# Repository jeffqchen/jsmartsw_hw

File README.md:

# jsmartsw_hw

This is the hardware repository of the jSmartSW project.

The hardware is consisted of two parts. The jSmartSW mainboard contains the main I/O and logic board. The keypad contains visual feedback interfaces and tactile inputs.

Detailed building guides and technical details are documented in the project wiki pages.

For functionality and day-to-day usage, please refer to the [main project repository](https://github.com/jeffqchen/jSmartSW)

## Primary Parts

### Main Board

The main board interfaces with and utilizes a Raspberry Pi Pico to run the logic programs of this project. The main board is needed for the project.

The main board has many ports for power and I/O:
- **Power**
  - **DC 5V barrel jack** (optional)

    The preferred source to power jSmartSW.
    
  - **USB-C jack** (optional)
 
    USB functionality is provided via this port. You can also power the jSmartSW from this port.

  - **Toggle switch** (optional)
    
    For turning the power from the barrel jack and USB-C jack on or off.

- **Video & Audio**
  - **HD15 video/audio passthrough input** (optional, recommended):
    
    Since the project communicates to the RetroTink 4K primarily via the HD15 port, you can connect HD15 sources to this port and feed it to the RetroTink 4K.
    
  - **HD15 video passthrough output** (optional):
    
    The video input from the passthrough input port is output from this port. The serial control commands are sent from this port to the RetroTink 4K if a USB-C connection is not present to the RetroTink 4K.
    
  - **3.5mm TRS barrel jack**:
    
    Audio signal input from the passthrough input pin 12 & 15 is broken out to this port, so you can use a 3.5mm TRS audio cable and feed it to the RetroTink 4K.

- **Communication**
  - **2x4 right-angle pin header**:
  
    Communicates with the gSCARTsw.
    
  - **2x7 right-angle pin header** (optional):

    Communicates with the optional keypad.
    
  - **HD15 video passthrough output** (already listed):

    The serial control commands are sent from this port to the RetroTink 4K if a USB-C connection is not present to the RetroTink 4K.
    
  - **USB-C jack** (already listed):

    When connected to the RetroTink 4K, it will become the preferred channel of communication. It also supplies power into the RetroTink 4K. In this case, the 5V barreljack must be populated as the main source of power.

### Keypad

The keypad is the primary user interface of jSmartSW. It has a screen, addressable RGB LEDs, and 8 key switches.

- Screen

  A 0.91 inch OLED SSD1306 screen at 128x32 resolution.

- 16 (8x2) WS2812b OR WS2812b 2020 addressable RGB LEDs.

  An array of addressabvle RGB LEDs for indicating device running state and prodiving visual assistance.
  
- 8x Cherry MX keyboard switches with XDA key caps

  An array of keyboard switches for controlling functionalities of jSmartSW.

- Keypad Faceplate Panel

  Cosmetic face panel with markings. Markings will be illuminated by the RGB LEDs.

- 3D printed Keypad body shell & light shroud

------
Shield: [![CC BY-SA 4.0][cc-by-sa-shield]][cc-by-sa]

This work is licensed under a
[Creative Commons Attribution-ShareAlike 4.0 International License][cc-by-sa].

[![CC BY-SA 4.0][cc-by-sa-image]][cc-by-sa]

[cc-by-sa]: http://creativecommons.org/licenses/by-sa/4.0/
[cc-by-sa-image]: https://licensebuttons.net/l/by-sa/4.0/88x31.png
[cc-by-sa-shield]: https://img.shields.io/badge/License-CC%20BY--SA%204.0-lightgrey.svg

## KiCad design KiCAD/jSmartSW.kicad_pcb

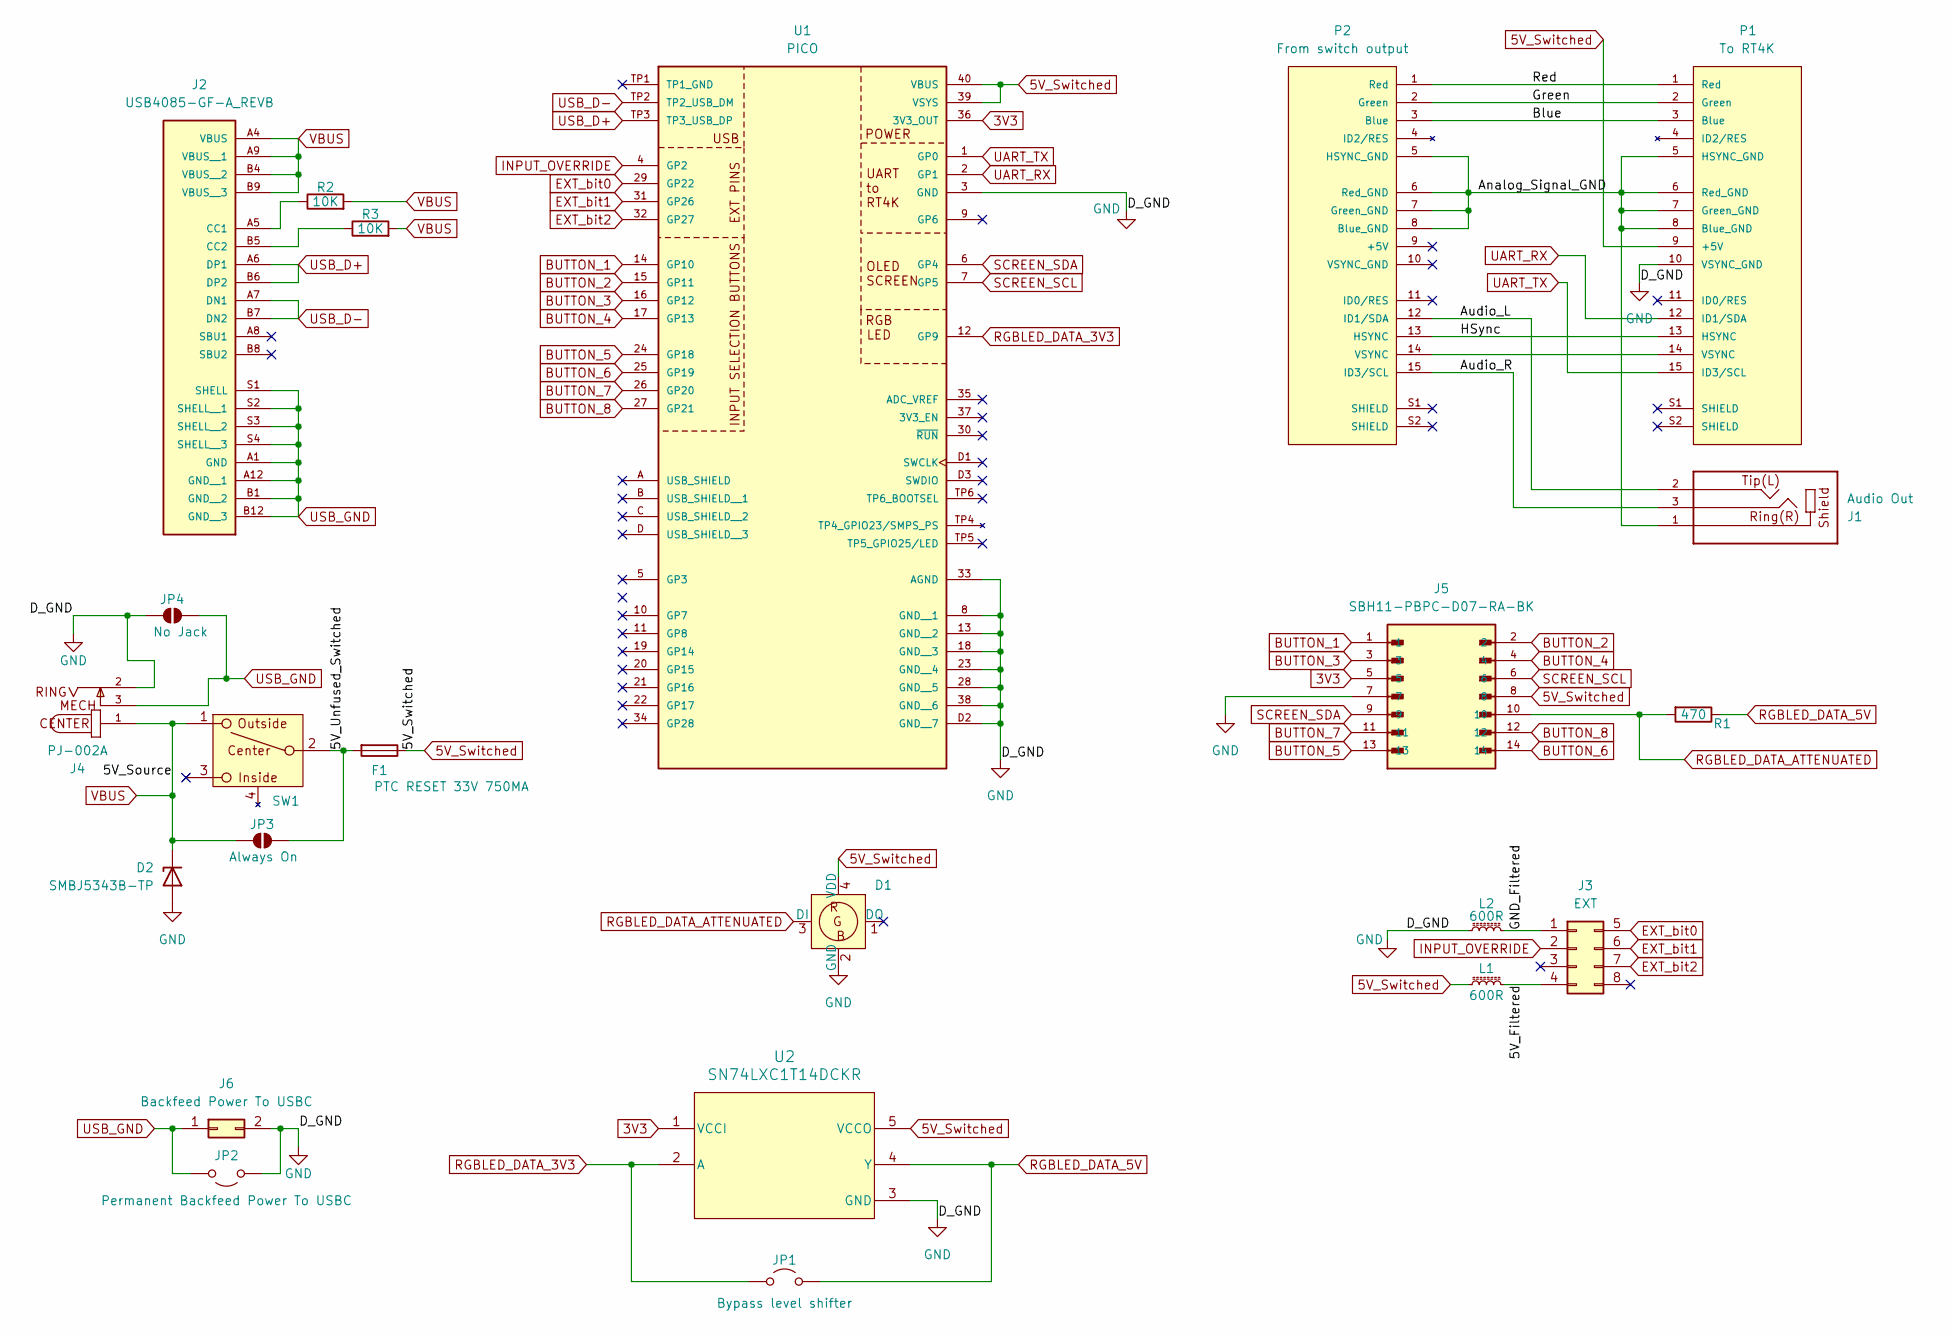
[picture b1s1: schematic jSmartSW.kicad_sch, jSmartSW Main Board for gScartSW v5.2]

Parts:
D1: WS2812b_2020
D2: SMBJ5343B-TP; D_SMB
F1: PTC RESET 33V 750MA; Fuse_1812_4532Metric_Pad1.30x3.40mm_HandSolder
J1: Audio Out; 3.5mm_jack_horizontal; PARTREV 1.02
J2: USB4085-GF-A_REVB; GCT_USB4085-GF-A_REVB; PARTREV B
J3: EXT; PinHeader_2x04_P2.54mm_Horizontal
J4: PJ-002A; CUI_PJ-002A
J5: SBH11-PBPC-D07-RA-BK; SULLINS_SBH11-PBPC-D07-RA-BK; PARTREV J
J6: Backfeed Power To USBC; PinHeader_1x02_P2.54mm_Horizontal
JP1: Bypass level shifter; SolderJumper-2_P1.3mm_Open_RoundedPad1.0x1.5mm
JP2: Permanent Backfeed Power To USBC; SolderJumper-2_P1.3mm_Bridged2Bar_RoundedPad1.0x1.5mm
JP3: Always On; SolderJumper-2_P1.3mm_Open_RoundedPad1.0x1.5mm
JP4: No Jack; SolderJumper-2_P1.3mm_Open_RoundedPad1.0x1.5mm
L1, L2: 600R; L_1206_3216Metric_Pad1.22x1.90mm_HandSolder
P1: To RT4K; VGA_female_rightangle_slim; PARTREV N/A
P2: From switch output; VGA_male_rightangle_slim; PARTREV N/A
R1: 470; R_0805_2012Metric_Pad1.20x1.40mm_HandSolder
R2, R3: 10K; R_0603_1608Metric_Pad0.98x0.95mm_HandSolder
SW1: BST13T1AVR
U1: PICO; RP2040_PICO; PARTREV 1.9
U2: SN74LXC1T14DCKR; DCK0005A-IPC_A

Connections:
3V3: J5.5, U1.36 (3V3_OUT), U2.1 (VCCI)
5V_Switched: D1.4 (VDD), F1.1, J5.8, L1.1, P1.9 (+5V), U1.39 (VSYS), U1.40 (VBUS), U2.5 (VCCO)
/5V_Filtered: J3.4, L1.2
/5V_Unfused_Switched: F1.2, JP3.1 (A), SW1.2 (Center)
/Analog_Signal_GND: J1.1, P1.5 (HSYNC_GND), P1.6 (Red_GND), P1.7 (Green_GND), P1.8 (Blue_GND), P2.5 (HSYNC_GND), P2.6 (Red_GND), P2.7 (Green_GND), P2.8 (Blue_GND)
/Audio_L: J1.2, P2.12 (ID1/SDA)
/Audio_R: J1.3, P2.15 (ID3/SCL)
/Blue: P1.3 (Blue), P2.3 (Blue)
/GND_Filtered: J3.1, L2.2
/Green: P1.2 (Green), P2.2 (Green)
/HSync: P1.13 (HSYNC), P2.13 (HSYNC)
/Red: P1.1 (Red), P2.1 (Red)
BUTTON_1: J5.1, U1.14 (GP10)
BUTTON_2: J5.2, U1.15 (GP11)
BUTTON_3: J5.3, U1.16 (GP12)
BUTTON_4: J5.4, U1.17 (GP13)
BUTTON_5: J5.13, U1.24 (GP18)
BUTTON_6: J5.14, U1.25 (GP19)
BUTTON_7: J5.11, U1.26 (GP20)
BUTTON_8: J5.12, U1.27 (GP21)
EXT_bit0: J3.5, U1.29 (GP22)
EXT_bit1: J3.6, U1.31 (GP26)
EXT_bit2: J3.7, U1.32 (GP27)
GND: D1.2 (GND), D2.2 (A), J4.2, J5.7, J6.2, JP2.1 (A), JP4.2 (B), L2.1, P1.10 (VSYNC_GND), U1.3 (GND), U1.8 (GND__1), U1.13 (GND__2), U1.18 (GND__3), U1.23 (GND__4), U1.28 (GND__5), U1.33 (AGND), U1.38 (GND__6), U1.D2 (GND__7), U2.3 (GND)
INPUT_OVERRIDE: J3.2, U1.4 (GP2)
unnamed: J2.A5 (CC1), R2.1
unnamed: J2.B5 (CC2), R3.1
unnamed: P1.14 (VSYNC), P2.14 (VSYNC)
RGBLED_DATA_3V3: JP1.1 (A), U1.12 (GP9), U2.2 (A)
RGBLED_DATA_5V: JP1.2 (B), R1.1, U2.4 (Y)
RGBLED_DATA_ATTENUATED: D1.3 (DI), J5.10, R1.2
SCREEN_SCL: J5.6, U1.7 (GP5)
SCREEN_SDA: J5.9, U1.6 (GP4)
UART_RX: P1.12 (ID1/SDA), U1.2 (GP1)
UART_TX: P1.15 (ID3/SCL), U1.1 (GP0)
USB_D+: J2.A6 (DP1), J2.B6 (DP2), U1.TP3 (TP3_USB_DP)
USB_D-: J2.A7 (DN1), J2.B7 (DN2), U1.TP2 (TP2_USB_DM)
USB_GND: J2.A1 (GND), J2.A12 (GND__1), J2.B1 (GND__2), J2.B12 (GND__3), J2.S1 (SHELL), J2.S2 (SHELL__1), J2.S3 (SHELL__2), J2.S4 (SHELL__3), J4.3, J6.1, JP2.2 (B), JP4.1 (A)
VBUS: D2.1 (K), J2.A4 (VBUS), J2.A9 (VBUS__1), J2.B4 (VBUS__2), J2.B9 (VBUS__3), J4.1, JP3.2 (B), R2.2, R3.2, SW1.1 (Outside)

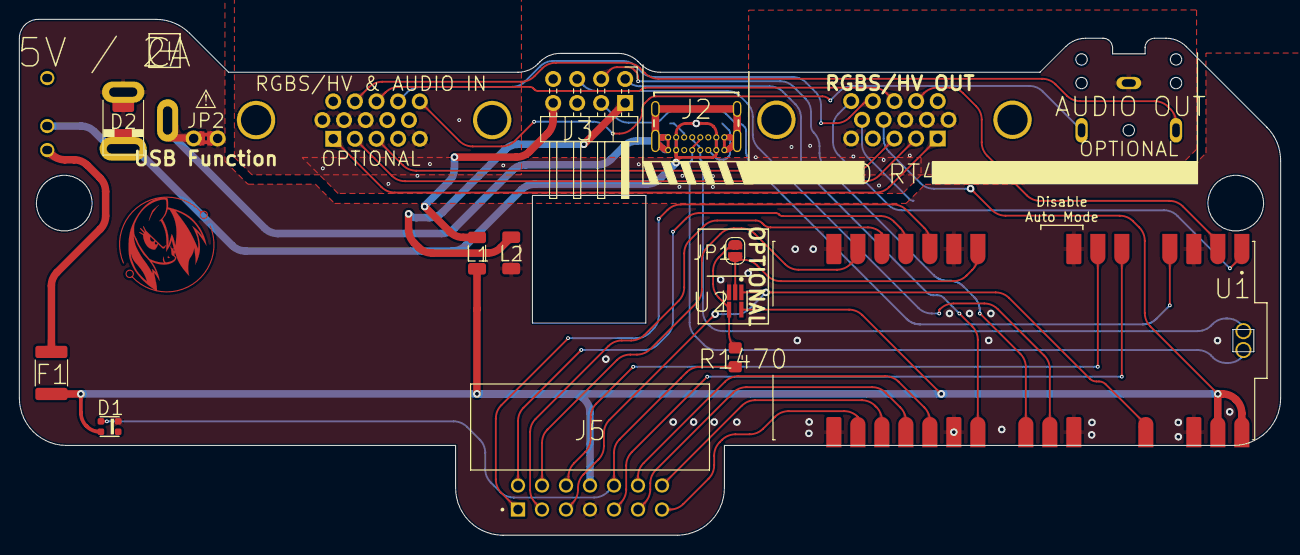
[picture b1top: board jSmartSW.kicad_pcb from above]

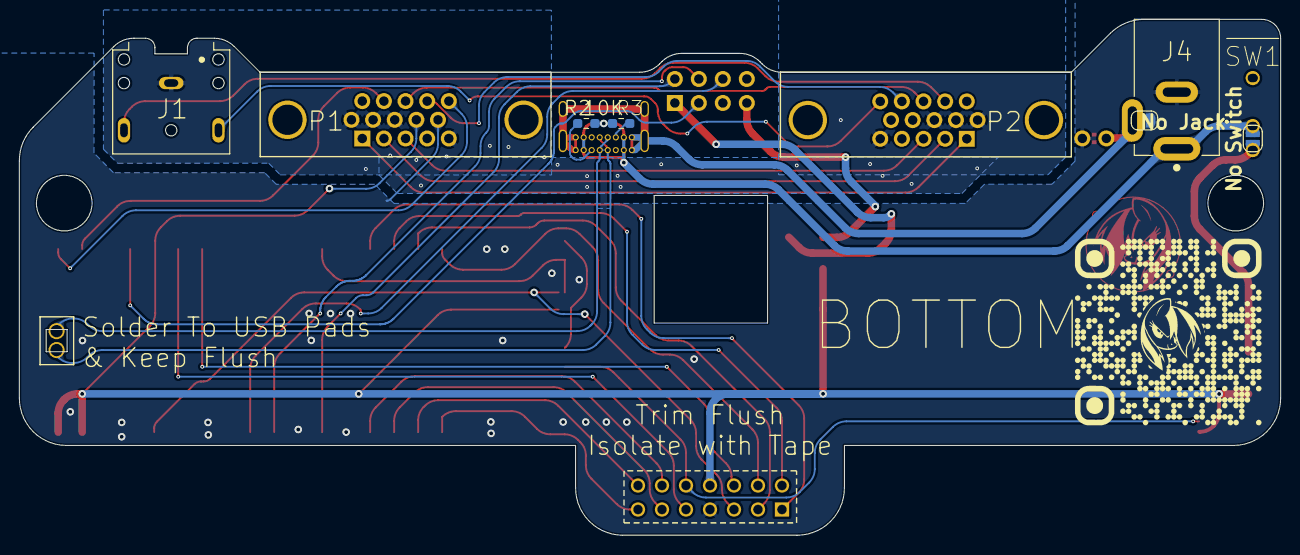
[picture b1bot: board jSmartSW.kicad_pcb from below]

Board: 2 copper layers, 133.5 x 54.6 mm, 23 parts (9 on the bottom side), 39 nets.

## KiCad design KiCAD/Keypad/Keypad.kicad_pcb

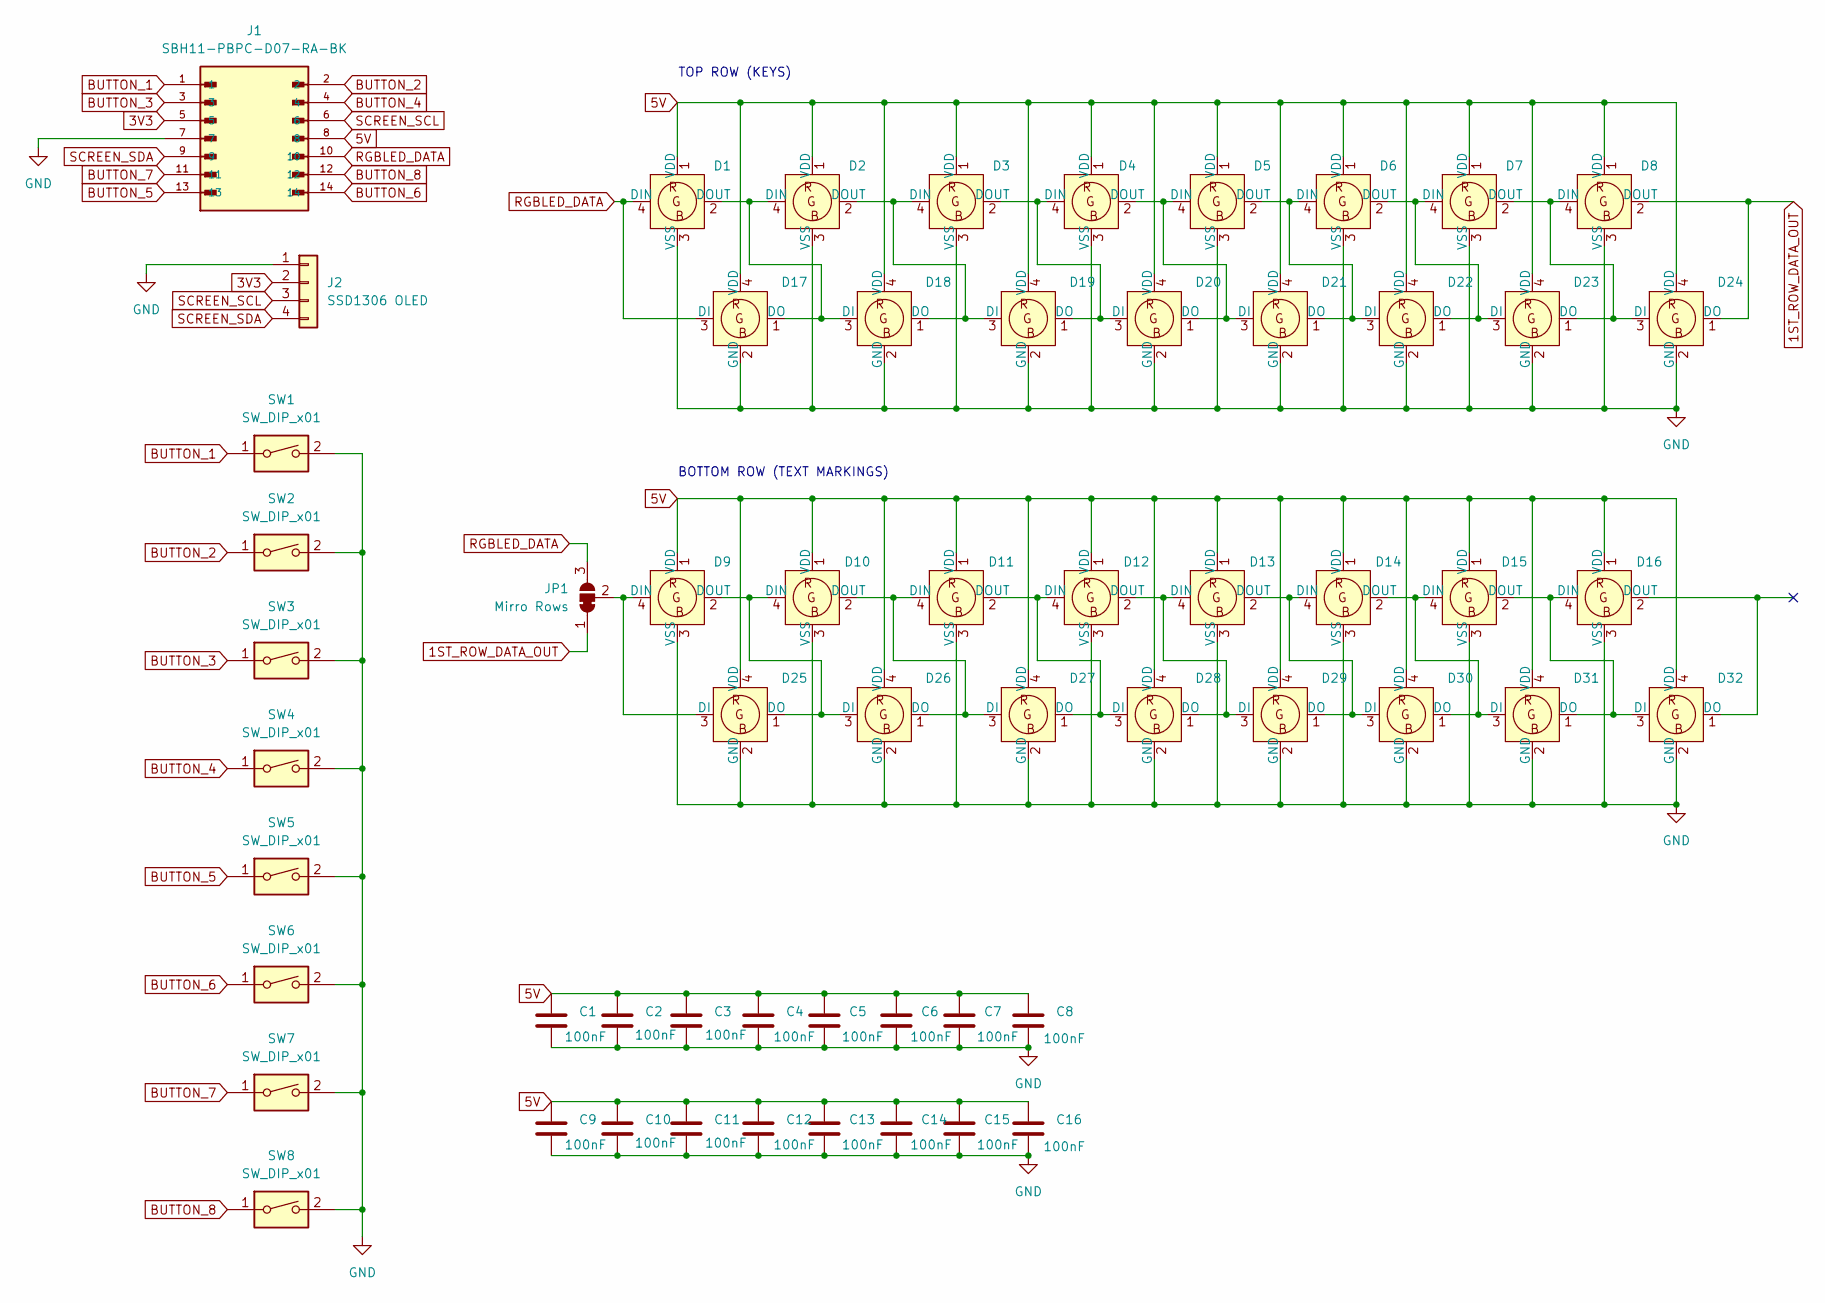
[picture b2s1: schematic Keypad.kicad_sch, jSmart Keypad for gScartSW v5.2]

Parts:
C1, C2, C3, C4, C5, C6, C7, C8, C9, C10, C11, C12, C13, C14, C15, C16: 100nF; R_0603_1608Metric_Pad0.98x0.95mm_HandSolder
D1, D2, D3, D4, D5, D6, D7, D8, D9, D10, D11, D12, D13, D14, D15, D16: WS2812B LED
D17, D18, D19, D20, D21, D22, D23, D24, D25, D26, D27, D28, D29, D30, D31, D32: WS2812b_2020
J1: SBH11-PBPC-D07-RA-BK; SULLINS_SBH11-PBPC-D07-RA-BK; PARTREV J
J2: SSD1306 OLED; PinHeader_1x04_P2.54mm_Vertical
JP1: Mirro Rows; SolderJumper-3_P1.3mm_Bridged2Bar12_RoundedPad1.0x1.5mm
SW1, SW2, SW3, SW4, SW5, SW6, SW7, SW8: SW_DIP_x01; SW_Cherry_MX_1.00u_Plate

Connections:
1ST_ROW_DATA_OUT: D8.2 (DOUT), D24.1 (DO), JP1.1 (A)
3V3: J1.5, J2.2
5V: C1.1, C2.1, C3.1, C4.1, C5.1, C6.1, C7.1, C8.1, C9.1, C10.1, C11.1, C12.1, C13.1, C14.1, C15.1, C16.1, D1.1 (VDD), D2.1 (VDD), D3.1 (VDD), D4.1 (VDD), D5.1 (VDD), D6.1 (VDD), D7.1 (VDD), D8.1 (VDD), D9.1 (VDD), D10.1 (VDD), D11.1 (VDD), D12.1 (VDD), D13.1 (VDD), D14.1 (VDD), D15.1 (VDD), D16.1 (VDD), D17.4 (VDD), D18.4 (VDD), D19.4 (VDD), D20.4 (VDD), D21.4 (VDD), D22.4 (VDD), D23.4 (VDD), D24.4 (VDD), D25.4 (VDD), D26.4 (VDD), D27.4 (VDD), D28.4 (VDD), D29.4 (VDD), D30.4 (VDD), D31.4 (VDD), D32.4 (VDD), J1.8
BUTTON_1: J1.1, SW1.1
BUTTON_2: J1.2, SW2.1
BUTTON_3: J1.3, SW3.1
BUTTON_4: J1.4, SW4.1
BUTTON_5: J1.13, SW5.1
BUTTON_6: J1.14, SW6.1
BUTTON_7: J1.11, SW7.1
BUTTON_8: J1.12, SW8.1
GND: C1.2, C2.2, C3.2, C4.2, C5.2, C6.2, C7.2, C8.2, C9.2, C10.2, C11.2, C12.2, C13.2, C14.2, C15.2, C16.2, D1.3 (VSS), D2.3 (VSS), D3.3 (VSS), D4.3 (VSS), D5.3 (VSS), D6.3 (VSS), D7.3 (VSS), D8.3 (VSS), D9.3 (VSS), D10.3 (VSS), D11.3 (VSS), D12.3 (VSS), D13.3 (VSS), D14.3 (VSS), D15.3 (VSS), D16.3 (VSS), D17.2 (GND), D18.2 (GND), D19.2 (GND), D20.2 (GND), D21.2 (GND), D22.2 (GND), D23.2 (GND), D24.2 (GND), D25.2 (GND), D26.2 (GND), D27.2 (GND), D28.2 (GND), D29.2 (GND), D30.2 (GND), D31.2 (GND), D32.2 (GND), J1.7, J2.1, SW1.2, SW2.2, SW3.2, SW4.2, SW5.2, SW6.2, SW7.2, SW8.2
unnamed: D1.2 (DOUT), D2.4 (DIN), D17.1 (DO), D18.3 (DI)
unnamed: D9.2 (DOUT), D10.4 (DIN), D25.1 (DO), D26.3 (DI)
unnamed: D10.2 (DOUT), D11.4 (DIN), D26.1 (DO), D27.3 (DI)
unnamed: D11.2 (DOUT), D12.4 (DIN), D27.1 (DO), D28.3 (DI)
unnamed: D12.2 (DOUT), D13.4 (DIN), D28.1 (DO), D29.3 (DI)
unnamed: D13.2 (DOUT), D14.4 (DIN), D29.1 (DO), D30.3 (DI)
unnamed: D14.2 (DOUT), D15.4 (DIN), D30.1 (DO), D31.3 (DI)
unnamed: D15.2 (DOUT), D16.4 (DIN), D31.1 (DO), D32.3 (DI)
unnamed: D2.2 (DOUT), D3.4 (DIN), D18.1 (DO), D19.3 (DI)
unnamed: D3.2 (DOUT), D4.4 (DIN), D19.1 (DO), D20.3 (DI)
unnamed: D4.2 (DOUT), D5.4 (DIN), D20.1 (DO), D21.3 (DI)
unnamed: D5.2 (DOUT), D6.4 (DIN), D21.1 (DO), D22.3 (DI)
unnamed: D6.2 (DOUT), D7.4 (DIN), D22.1 (DO), D23.3 (DI)
unnamed: D7.2 (DOUT), D8.4 (DIN), D23.1 (DO), D24.3 (DI)
unnamed: D9.4 (DIN), D25.3 (DI), JP1.2 (C)
RGBLED_DATA: D1.4 (DIN), D17.3 (DI), J1.10, JP1.3 (B)
SCREEN_SCL: J1.6, J2.3
SCREEN_SDA: J1.9, J2.4

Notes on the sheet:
TOP ROW (KEYS)
BOTTOM ROW (TEXT MARKINGS)

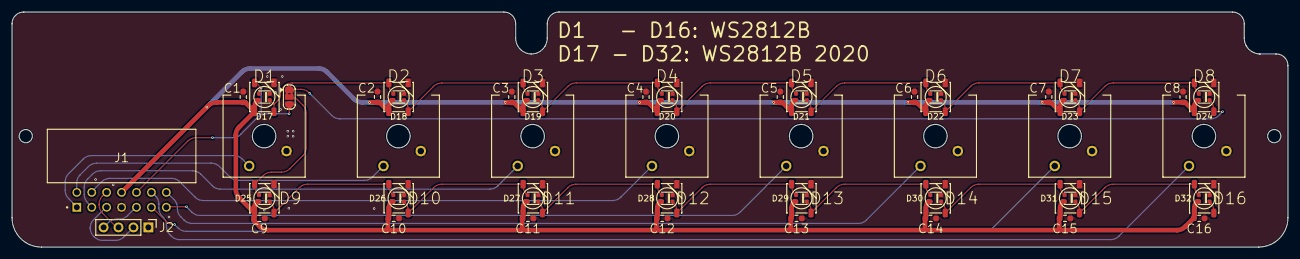
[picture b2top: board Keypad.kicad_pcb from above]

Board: 2 copper layers, 217.2 x 40.0 mm, 59 parts (0 on the bottom side), 30 nets.

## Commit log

2025-04-15 Initial Version
2025-04-20 3D Print STL files
2025-05-08 Update Keypad Bottom Plate.stl
    Improve model fitness
2025-05-27 Update Main PCB Silkscreen
2025-11-11 Add Creative Commons License
    Added the Creative Commons Attribution-ShareAlike 4.0 International Public License to the project.
2025-11-11 Add Creative Commons license information to README
    Added licensing information and badge for Creative Commons.
